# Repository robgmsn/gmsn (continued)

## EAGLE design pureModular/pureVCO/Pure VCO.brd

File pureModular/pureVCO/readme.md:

DESIGN STATUS: Awaiting testing - Ready for beta testing.

VCO Updated to V3.1 14/04/21.

Mixer section changed from Average to Sum. Mix Out is now inversion of individual outs. Might be useful?
Resistor values around mixer section reduced to 10k, inline with low noise techniques.

To do:
Final test build

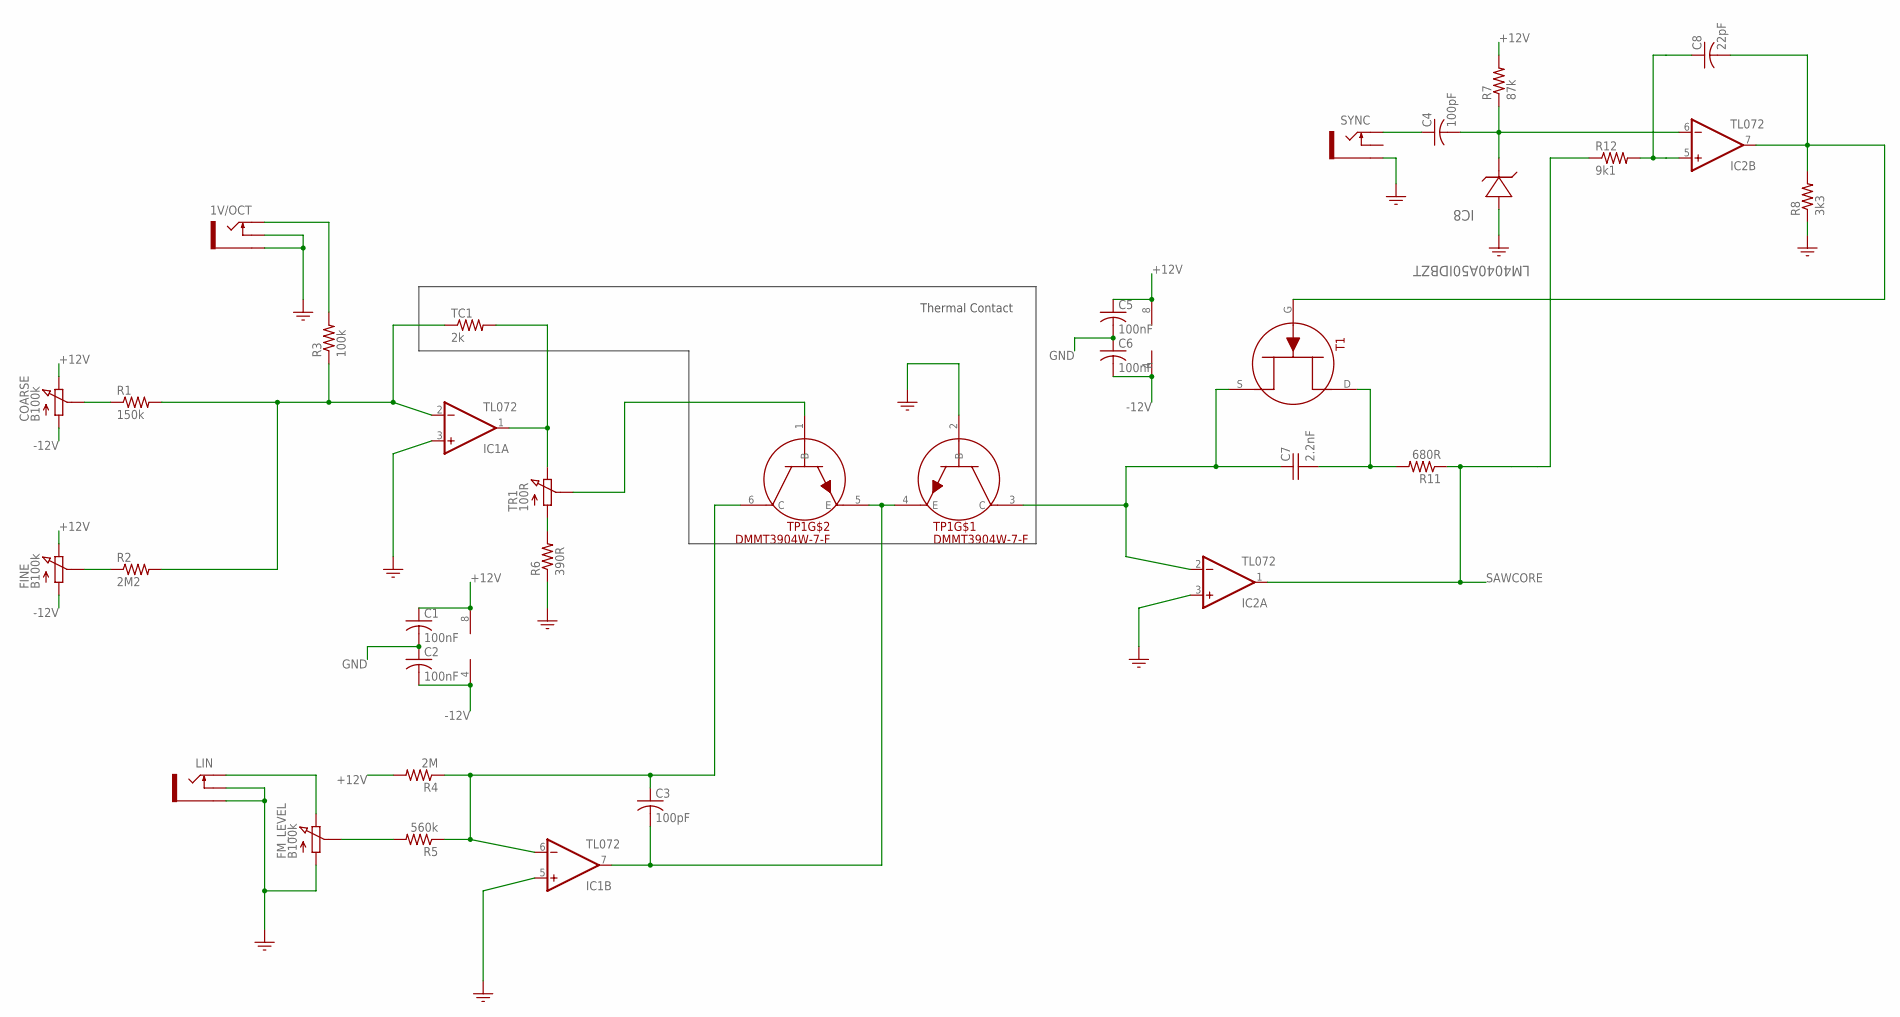
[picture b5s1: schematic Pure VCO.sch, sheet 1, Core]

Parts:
1V/OCT: PJ301M-12
C1, C2, C5, C6: 100nF; C0805
C3, C4: 100pF; C0805
C7: 2.2nF; POLY_CAP
C8: 22pF; C0805
COARSE: B100k; POT_9MM_RED_KNOB
FINE: B100k; POT_9MM_RED_MXR_KNOB
FM_LEVEL: B100k; POT_9MM_GREEN_KNOB
IC1, IC2: TL072; SO08
IC8: LM4040A50IDBZT; SOT95P237X112-3N
LIN: PJ301M-12
R1: 150k; R0805
R2: 2M2; R0805
R3: 100k; R0805
R4: 2M; R0805
R5: 560k; R0805
R6: 390R; R0805
R7: 87k; R0805
R8: 3k3; R0805
R11: 680R; R0805
R12: 9k1; R0805
SYNC: PJ301M-12
T1: MMBFJ309; N_CHN
TC1: 2k; 0207/8.5
TP1: DMMT3904W-7-F; TRANS_PAIR
TR1: 100R; TRIMMER_TH

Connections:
+12V: C1.1, C5.1, COARSE.P$3 (3), FINE.P$3 (3), IC1.8 (V+), IC2.8 (V+), R4.2, R7.2; also elsewhere on the board
-12V: C2.2, C6.2, COARSE.P$1 (1), FINE.P$1 (1), IC1.4 (V-), IC2.4 (V-); also elsewhere on the board
GND: 1V/OCT.GND (SLEEVE), 1V/OCT.NORM (SWITCH), C1.2, C2.1, C5.2, C6.1, FM_LEVEL.P$1 (1), IC1.3 (+IN), IC1.5 (+IN), IC2.3 (+IN), IC8.2 (ANODE), LIN.GND (SLEEVE), LIN.NORM (SWITCH), R6.1, R8.1, SYNC.GND (SLEEVE), TP1.2 (B); also elsewhere on the board
unnamed: COARSE.P$2 (2), R1.1
unnamed: IC1.2 (-IN), R1.2, R2.2, R3.1, TC1.1
unnamed: FINE.P$2 (2), R2.1
unnamed: IC1.1 (OUT), TC1.2, TR1.3
unnamed: R6.2, TR1.1
unnamed: 1V/OCT.TIP, R3.2
unnamed: TP1.1 (B), TR1.2
unnamed: C7.2 (-), R11.2, T1.D
unnamed: C3.1, IC1.6 (-IN), R4.1, R5.1, TP1.6 (C)
unnamed: C7.1 (+), IC2.2 (-IN), T1.S, TP1.3 (C)
unnamed: FM_LEVEL.P$3 (3), LIN.TIP
unnamed: C8.1, IC2.5 (+IN), R12.2
unnamed: FM_LEVEL.P$2 (2), R5.2
unnamed: C3.2, IC1.7 (OUT), TP1.4 (E), TP1.5 (E)
unnamed: C8.2, IC2.7 (OUT), R8.2, T1.G
unnamed: C4.1, SYNC.TIP
unnamed: C4.2, IC2.6 (-IN), IC8.1 (CATHODE), R7.1
SAWCORE: IC2.1 (OUT), R11.1, R12.1; also elsewhere on the board

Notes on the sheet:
Thermal Contact

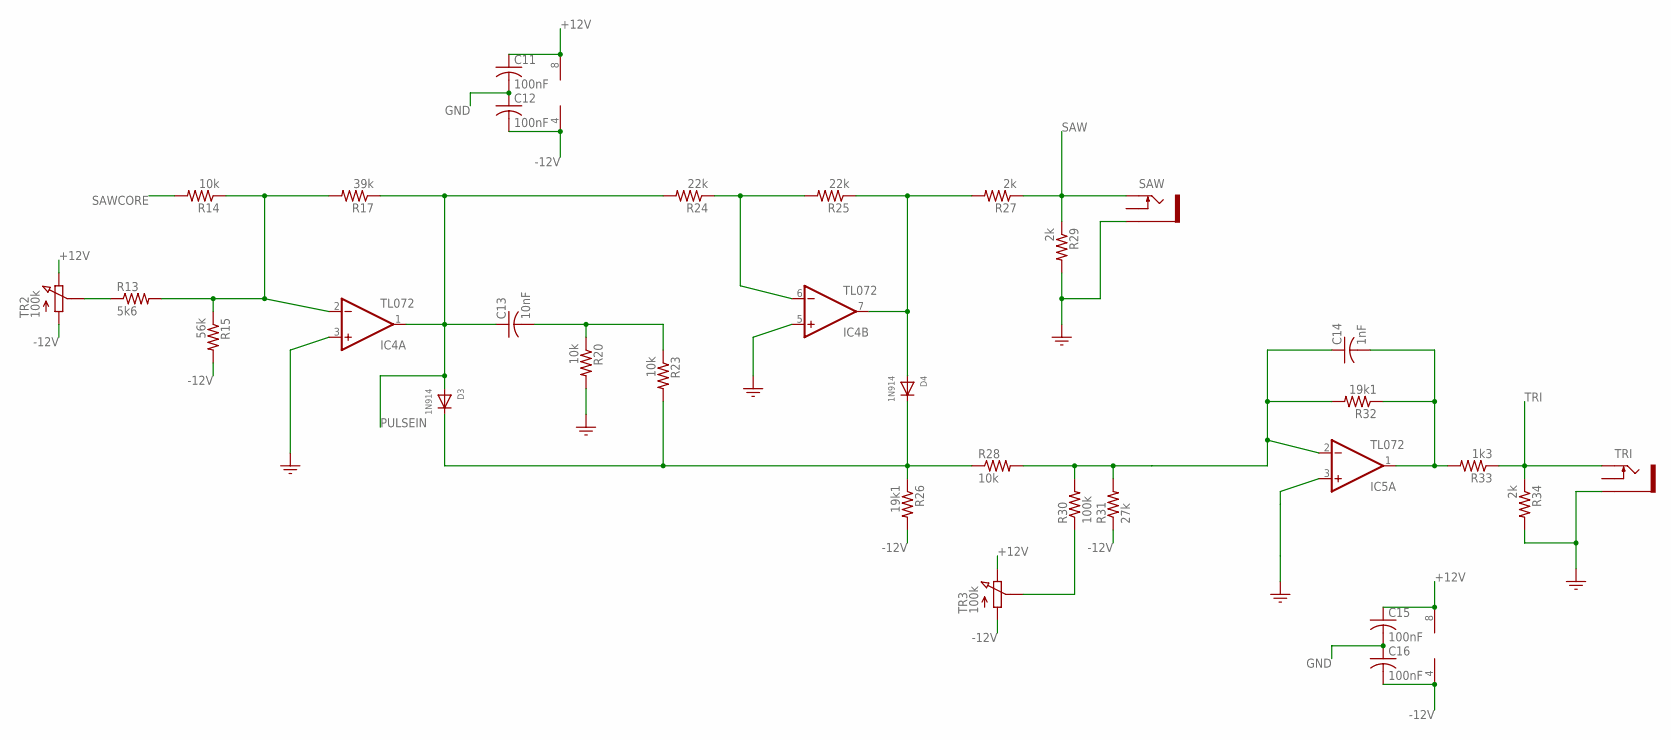
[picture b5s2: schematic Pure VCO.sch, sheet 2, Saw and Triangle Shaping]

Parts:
C11, C12, C15, C16: 100nF; C0805
C13: 10nF; C0805
C14: 1nF; C0805
D3, D4: 1N914; SOD-323F
IC4, IC5: TL072; SO08
R13: 5k6; R0805
R14, R20, R23, R28: 10k; R0805
R15: 56k; R0805
R17: 39k; R0805
R24, R25: 22k; R0805
R26, R32: 19k1; R0805
R27, R29, R34: 2k; R0805
R30: 100k; R0805
R31: 27k; R0805
R33: 1k3; R0805
SAW: PJ301M-12
TR2, TR3: 100k; TRIMMER_TH
TRI: PJ301M-12

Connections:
+12V: C11.1, C15.1, IC4.8 (V+), IC5.8 (V+), TR2.3, TR3.3; also elsewhere on the board
-12V: C12.2, C16.2, IC4.4 (V-), IC5.4 (V-), R15.2, R26.2, R31.1, TR2.1, TR3.1; also elsewhere on the board
GND: C11.2, C12.1, C15.2, C16.1, IC4.3 (+IN), IC4.5 (+IN), IC5.3 (+IN), R20.2, R29.2, R34.2, SAW.GND (SLEEVE), TRI.GND (SLEEVE); also elsewhere on the board
unnamed: R13.1, TR2.2
unnamed: IC4.2 (-IN), R13.2, R14.1, R15.1, R17.2
unnamed: C13.2, R20.1, R23.1
unnamed: R30.1, TR3.2
unnamed: IC4.6 (-IN), R24.1, R25.2
unnamed: D4.A, IC4.7 (OUT), R25.1, R27.2
unnamed: D3.C, D4.C, R23.2, R26.1, R28.1
unnamed: C14.1, IC5.2 (-IN), R28.2, R30.2, R31.2, R32.2
unnamed: C14.2, IC5.1 (OUT), R32.1, R33.2
PULSEIN: C13.1, D3.A, IC4.1 (OUT), R17.1, R24.2; also elsewhere on the board
SAW: R27.1, R29.1, SAW.TIP; also elsewhere on the board
SAWCORE: R14.2; also elsewhere on the board
TRI: R33.1, R34.1, TRI.TIP; also elsewhere on the board

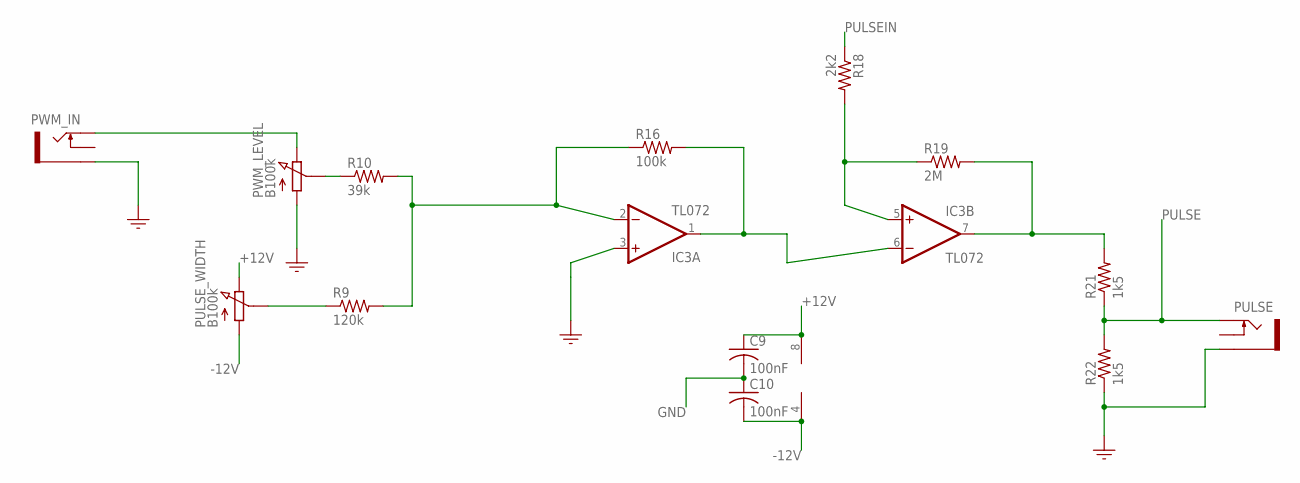
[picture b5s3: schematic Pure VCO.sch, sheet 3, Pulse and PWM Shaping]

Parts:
C9, C10: 100nF; C0805
IC3: TL072; SO08
PULSE: PJ301M-12
PULSE_WIDTH: B100k; POT_9MM_YELLOW_KNOB
PWM_IN: PJ301M-12
PWM_LEVEL: B100k; POT_9MM_GREEN_KNOB
R9: 120k; R0805
R10: 39k; R0805
R16: 100k; R0805
R18: 2k2; R0805
R19: 2M; R0805
R21, R22: 1k5; R0805

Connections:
+12V: C9.1, IC3.8 (V+), PULSE_WIDTH.P$3 (3); also elsewhere on the board
-12V: C10.2, IC3.4 (V-), PULSE_WIDTH.P$1 (1); also elsewhere on the board
GND: C9.2, C10.1, IC3.3 (+IN), PULSE.GND (SLEEVE), PWM_IN.GND (SLEEVE), PWM_LEVEL.P$1 (1), R22.1; also elsewhere on the board
unnamed: IC3.1 (OUT), IC3.6 (-IN), R16.2
unnamed: IC3.5 (+IN), R18.2, R19.1
unnamed: IC3.7 (OUT), R19.2, R21.2
unnamed: PULSE_WIDTH.P$2 (2), R9.1
unnamed: PWM_IN.TIP, PWM_LEVEL.P$3 (3)
unnamed: IC3.2 (-IN), R9.2, R10.2, R16.1
unnamed: PWM_LEVEL.P$2 (2), R10.1
PULSE: PULSE.TIP, R21.1, R22.2; also elsewhere on the board
PULSEIN: R18.1; also elsewhere on the board

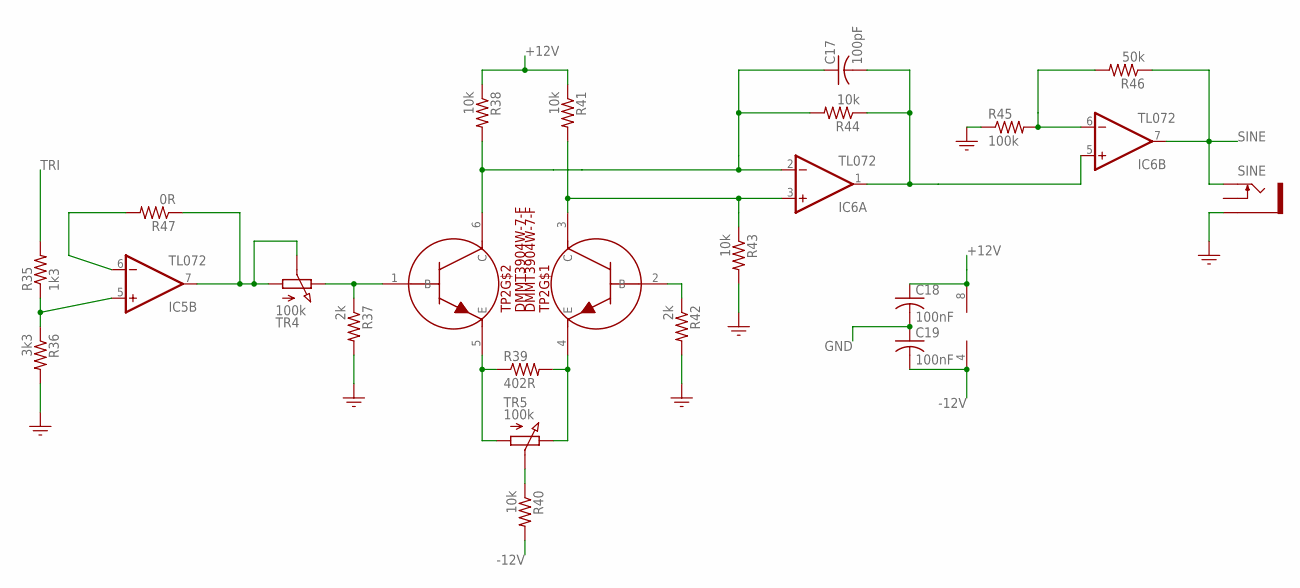
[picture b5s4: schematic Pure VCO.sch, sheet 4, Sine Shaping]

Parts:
C17: 100pF; C0805
C18, C19: 100nF; C0805
IC5, IC6: TL072; SO08
R35: 1k3; R0805
R36: 3k3; R0805
R37, R42: 2k; R0805
R38, R40, R41, R43, R44: 10k; R0805
R39: 402R; R0805
R45: 100k; R0805
R46: 50k; R0805
R47: 0R; R0805
SINE: PJ301M-12
TP2: DMMT3904W-7-F; TRANS_PAIR
TR4, TR5: 100k; TRIMMER_TH

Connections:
+12V: C18.1, IC6.8 (V+), R38.1, R41.1; also elsewhere on the board
-12V: C19.2, IC6.4 (V-), R40.2; also elsewhere on the board
GND: C18.2, C19.1, R36.2, R37.2, R42.2, R43.2, R45.1, SINE.GND (SLEEVE); also elsewhere on the board
unnamed: C17.1, IC6.2 (-IN), R38.2, R44.2, TP2.6 (C)
unnamed: IC5.6 (-IN), R47.2
unnamed: IC5.7 (OUT), R47.1, TR4.1, TR4.2
unnamed: R37.1, TP2.1 (B), TR4.3
unnamed: R39.1, TP2.5 (E), TR5.1
unnamed: R39.2, TP2.4 (E), TR5.3
unnamed: R40.1, TR5.2
unnamed: R42.1, TP2.2 (B)
unnamed: IC6.3 (+IN), R41.2, R43.1, TP2.3 (C)
unnamed: IC5.5 (+IN), R35.1, R36.1
unnamed: IC6.6 (-IN), R45.2, R46.2
SINE: IC6.7 (OUT), R46.1, SINE.TIP; also elsewhere on the board
SINE_PRE1: C17.2, IC6.1 (OUT), IC6.5 (+IN), R44.1
TRI: R35.2; also elsewhere on the board

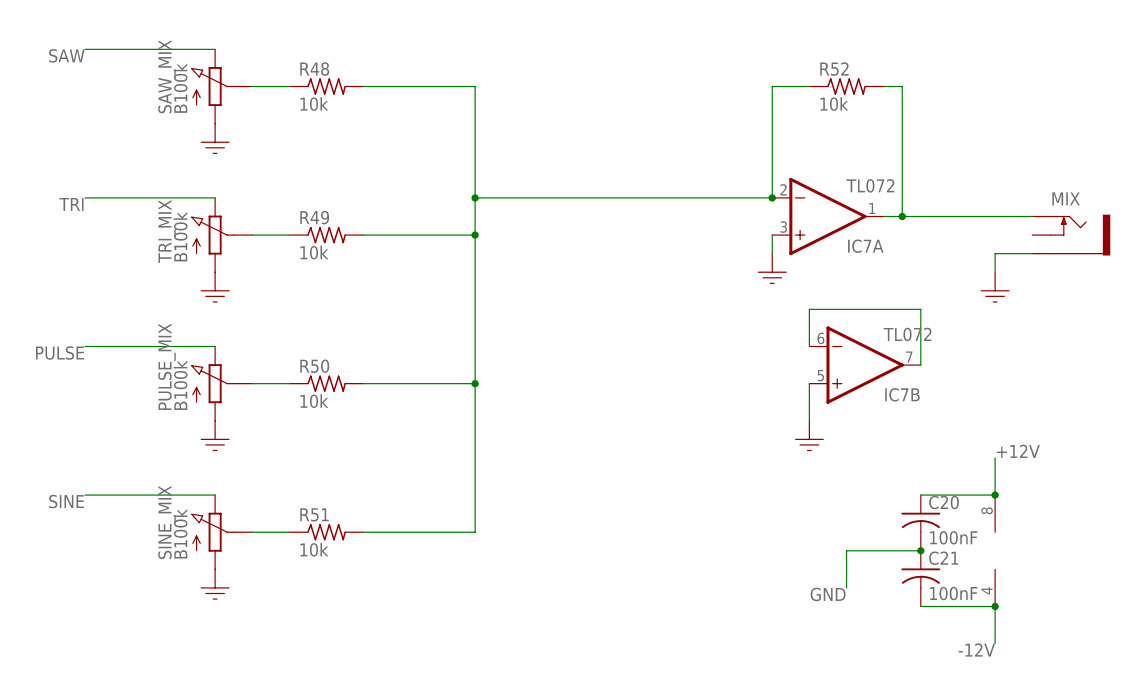
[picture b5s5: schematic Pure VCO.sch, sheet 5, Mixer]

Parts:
C20, C21: 100nF; C0805
IC7: TL072; SO08
MIX: PJ301M-12
PULSE_MIX: B100k; POT_9MM_BLUE_KNOB
R48, R49, R50, R51, R52: 10k; R0805
SAW_MIX: B100k; POT_9MM_BLUE_KNOB
SINE_MIX: B100k; POT_9MM_BLUE_KNOB
TRI_MIX: B100k; POT_9MM_BLUE_KNOB

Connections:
+12V: C20.1, IC7.8 (V+); also elsewhere on the board
-12V: C21.2, IC7.4 (V-); also elsewhere on the board
GND: C20.2, C21.1, IC7.3 (+IN), IC7.5 (+IN), MIX.GND (SLEEVE), PULSE_MIX.P$1 (1), SAW_MIX.P$1 (1), SINE_MIX.P$1 (1), TRI_MIX.P$1 (1); also elsewhere on the board
unnamed: IC7.6 (-IN), IC7.7 (OUT)
unnamed: R48.1, SAW_MIX.P$2 (2)
unnamed: R49.1, TRI_MIX.P$2 (2)
unnamed: PULSE_MIX.P$2 (2), R50.1
unnamed: R51.1, SINE_MIX.P$2 (2)
unnamed: IC7.2 (-IN), R48.2, R49.2, R50.2, R51.2, R52.1
unnamed: IC7.1 (OUT), MIX.TIP, R52.2
PULSE: PULSE_MIX.P$3 (3); also elsewhere on the board
SAW: SAW_MIX.P$3 (3); also elsewhere on the board
SINE: SINE_MIX.P$3 (3); also elsewhere on the board
TRI: TRI_MIX.P$3 (3); also elsewhere on the board

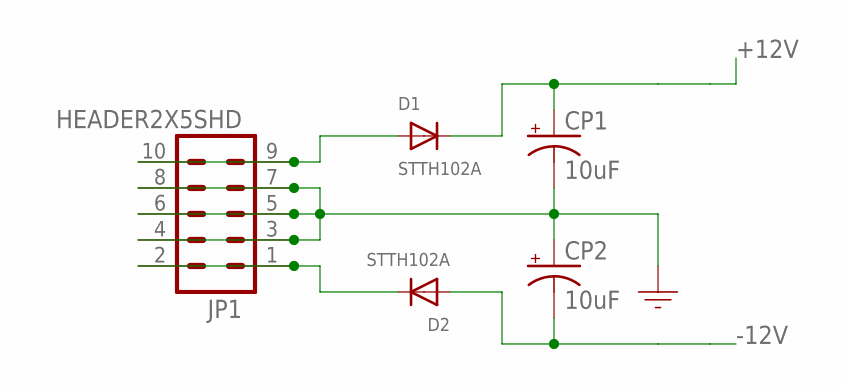
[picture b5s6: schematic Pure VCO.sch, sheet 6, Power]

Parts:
CP1, CP2: 10uF; 153CLV-0505
D1, D2: STTH102A; SMADIODE
JP1: HEADER2X5SHD; 2X5-SHROUDED

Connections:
+12V: CP1.+, D1.C; also elsewhere on the board
-12V: CP2.-, D2.A; also elsewhere on the board
GND: CP1.-, CP2.+, JP1.3, JP1.4, JP1.5, JP1.6, JP1.7, JP1.8; also elsewhere on the board
unnamed: D1.A, JP1.9, JP1.10
unnamed: D2.C, JP1.1, JP1.2

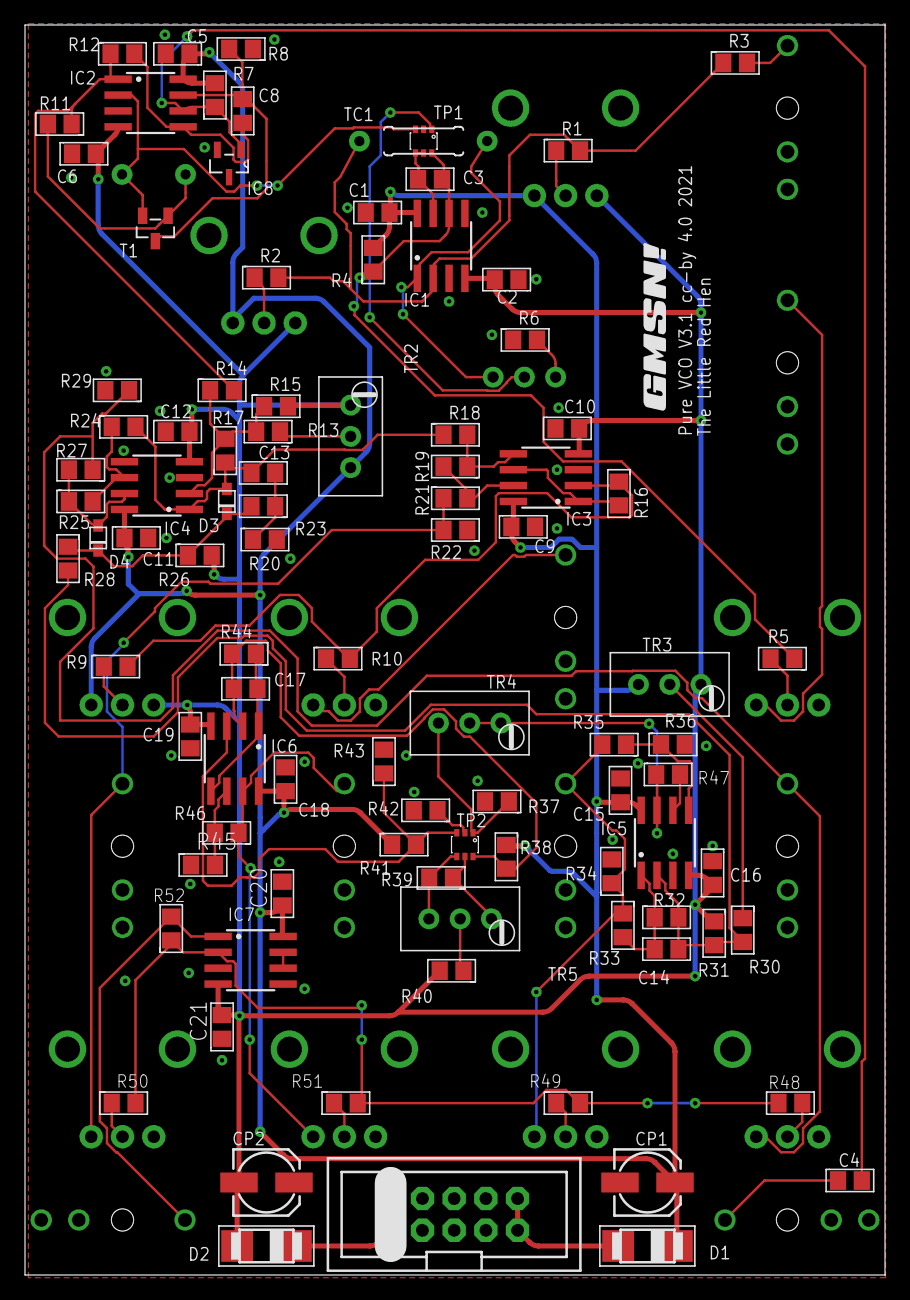
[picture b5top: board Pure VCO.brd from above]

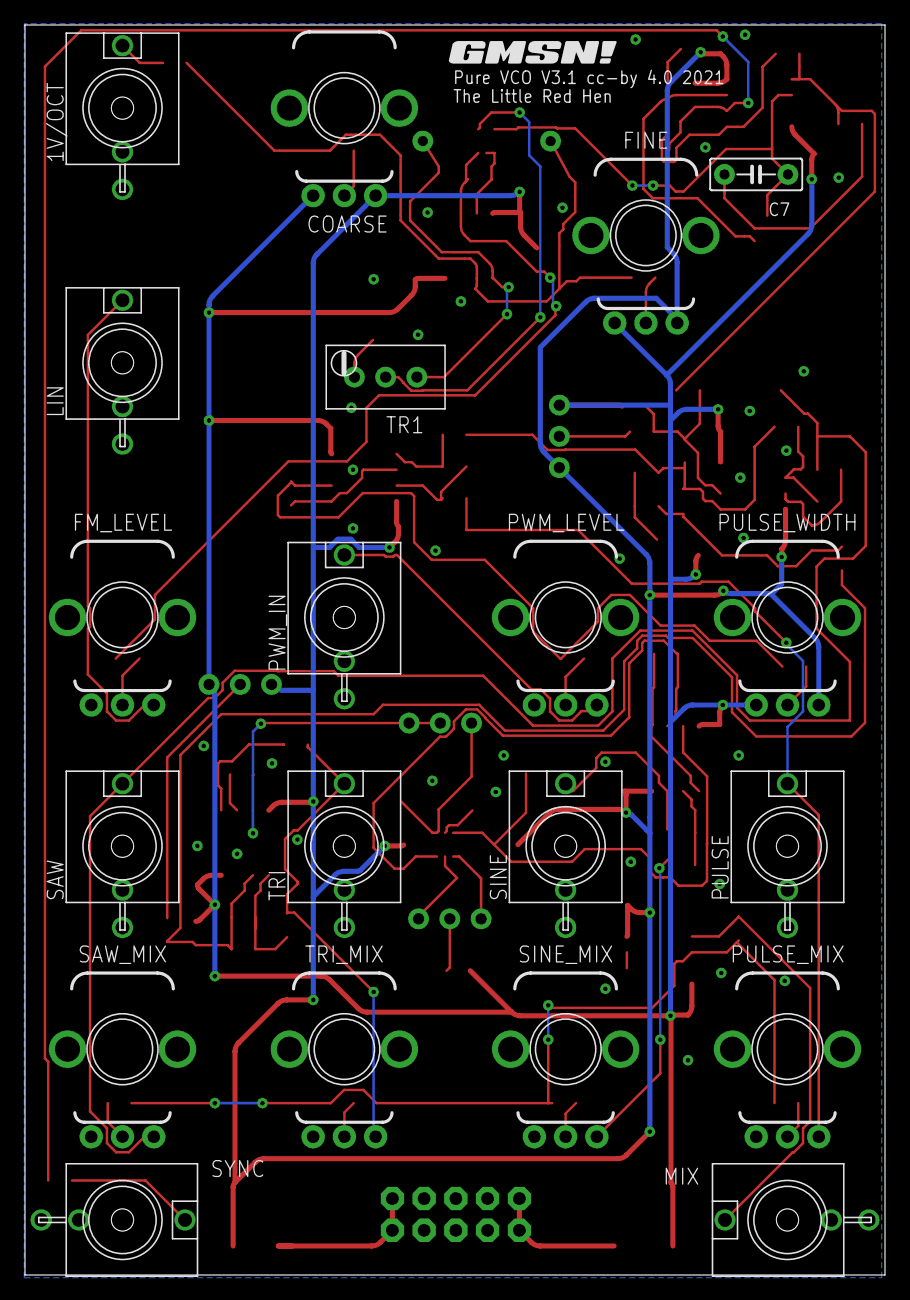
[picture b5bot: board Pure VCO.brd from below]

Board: 2 copper layers, 68.8 x 100.0 mm, 117 parts (21 on the bottom side), 63 nets.

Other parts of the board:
U$1, U$2: GMSN!_LOGO

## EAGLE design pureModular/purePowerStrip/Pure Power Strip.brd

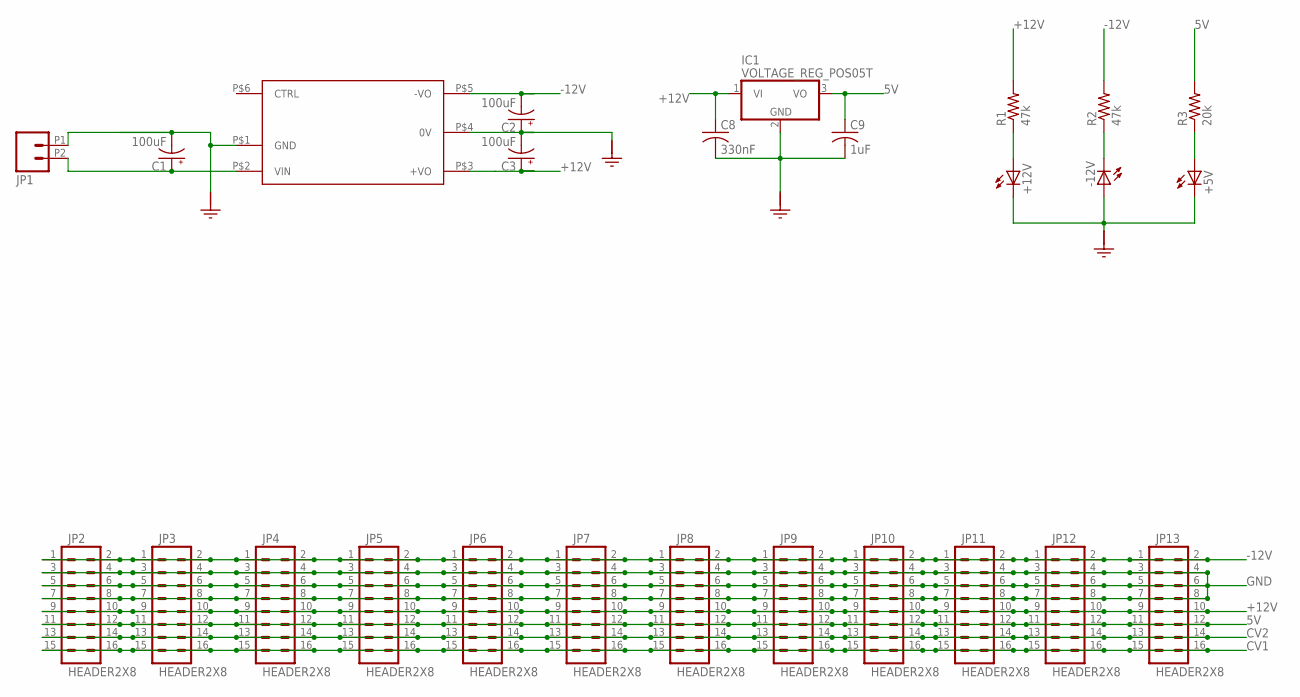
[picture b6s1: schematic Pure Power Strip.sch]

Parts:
+5V, +12V: LED5MM
-12V: LED5MM
C1, C2, C3: 100uF; 0511/2.24
C8: 330nF; C025-024X044
C9: 1uF; C025-024X044
IC1: VOLTAGE_REG_POS05T; TO220H
JP1: HEADER1X25MM_SCREWTERM; 1X02_5MM_SCREWTERM
JP2, JP3, JP4, JP5, JP6, JP7, JP8, JP9, JP10, JP11, JP12, JP13: HEADER2X8; POWER_SHROUDED
R1, R2: 47k; 0207/8.5
R3: 20k; 0207/8.5
U$1: DCDC_CONVERTER_URA241XLD-20WR3; URA241XLD-20WR3

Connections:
5V: C9.1, IC1.3 (VO), JP2.11, JP2.12, JP3.11, JP3.12, JP4.11, JP4.12, JP5.11, JP5.12, JP6.11, JP6.12, JP7.11, JP7.12, JP8.11, JP8.12, JP9.11, JP9.12, JP10.11, JP10.12, JP11.11, JP11.12, JP12.11, JP12.12, JP13.11, JP13.12, R3.2
+12V: C3.P$2 (+), C8.1, IC1.1 (VI), JP2.9, JP2.10, JP3.9, JP3.10, JP4.9, JP4.10, JP5.9, JP5.10, JP6.9, JP6.10, JP7.9, JP7.10, JP8.9, JP8.10, JP9.9, JP9.10, JP10.9, JP10.10, JP11.9, JP11.10, JP12.9, JP12.10, JP13.9, JP13.10, R1.2, U$1.P$3 (+VO)
-12V: C2.P$1 (-), JP2.1, JP2.2, JP3.1, JP3.2, JP4.1, JP4.2, JP5.1, JP5.2, JP6.1, JP6.2, JP7.1, JP7.2, JP8.1, JP8.2, JP9.1, JP9.2, JP10.1, JP10.2, JP11.1, JP11.2, JP12.1, JP12.2, JP13.1, JP13.2, R2.2, U$1.P$5 (-VO)
CV1: JP2.15, JP2.16, JP3.15, JP3.16, JP4.15, JP4.16, JP5.15, JP5.16, JP6.15, JP6.16, JP7.15, JP7.16, JP8.15, JP8.16, JP9.15, JP9.16, JP10.15, JP10.16, JP11.15, JP11.16, JP12.15, JP12.16, JP13.15, JP13.16
CV2: JP2.13, JP2.14, JP3.13, JP3.14, JP4.13, JP4.14, JP5.13, JP5.14, JP6.13, JP6.14, JP7.13, JP7.14, JP8.13, JP8.14, JP9.13, JP9.14, JP10.13, JP10.14, JP11.13, JP11.14, JP12.13, JP12.14, JP13.13, JP13.14
GND: +5V.K (C), +12V.K (C), -12V.A, C1.P$1 (-), C2.P$2 (+), C3.P$1 (-), C8.2, C9.2, IC1.2 (GND), JP1.P1 (1), JP2.3, JP2.4, JP2.5, JP2.6, JP2.7, JP2.8, JP3.3, JP3.4, JP3.5, JP3.6, JP3.7, JP3.8, JP4.3, JP4.4, JP4.5, JP4.6, JP4.7, JP4.8, JP5.3, JP5.4, JP5.5, JP5.6, JP5.7, JP5.8, JP6.3, JP6.4, JP6.5, JP6.6, JP6.7, JP6.8, JP7.3, JP7.4, JP7.5, JP7.6, JP7.7, JP7.8, JP8.3, JP8.4, JP8.5, JP8.6, JP8.7, JP8.8, JP9.3, JP9.4, JP9.5, JP9.6, JP9.7, JP9.8, JP10.3, JP10.4, JP10.5, JP10.6, JP10.7, JP10.8, JP11.3, JP11.4, JP11.5, JP11.6, JP11.7, JP11.8, JP12.3, JP12.4, JP12.5, JP12.6, JP12.7, JP12.8, JP13.3, JP13.4, JP13.5, JP13.6, JP13.7, JP13.8, U$1.P$1 (GND), U$1.P$4 (0V)
unnamed: C1.P$2 (+), JP1.P2 (2), U$1.P$2 (VIN)
unnamed: +12V.A, R1.1
unnamed: -12V.K (C), R2.1
unnamed: +5V.A, R3.1

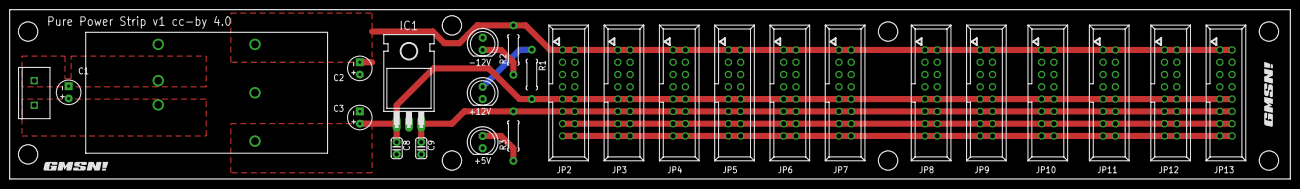
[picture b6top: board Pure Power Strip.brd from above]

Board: 2 copper layers, 264.8 x 35.0 mm, 28 parts (0 on the bottom side), 10 nets.

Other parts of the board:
U$14, U$15: GMSN!_LOGO

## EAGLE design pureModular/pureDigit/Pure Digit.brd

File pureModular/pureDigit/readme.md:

Awaiting Testing - Not for public consumption.

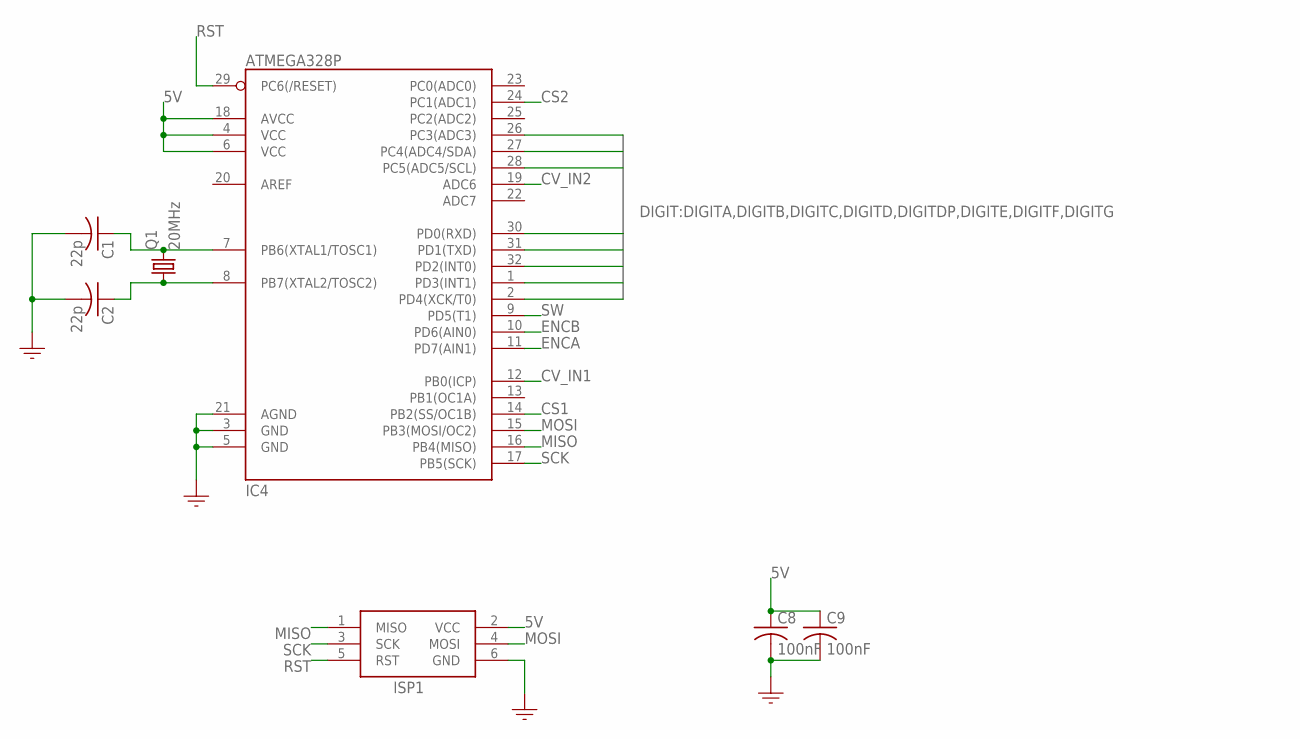
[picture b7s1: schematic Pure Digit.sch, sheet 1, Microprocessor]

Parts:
C1, C2: 22p; C0805
C8, C9: 100nF; C0805
IC4: ATMEGA328P; TQFP32-08
ISP1: HEADER2X3-6; AVRISP
Q1: 20MHz; SM49

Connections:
5V: C8.1, C9.1, IC4.4 (VCC), IC4.6 (VCC), IC4.18 (AVCC), ISP1.2 (VCC); also elsewhere on the board
CS1: IC4.14 (PB2(SS/OC1B)); also elsewhere on the board
CS2: IC4.24 (PC1(ADC1)); also elsewhere on the board
CV_IN1: IC4.12 (PB0(ICP)); also elsewhere on the board
CV_IN2: IC4.19 (ADC6); also elsewhere on the board
DIGITA: IC4.30 (PD0(RXD)); also elsewhere on the board
DIGITB: IC4.28 (PC5(ADC5/SCL)); also elsewhere on the board
DIGITC: IC4.27 (PC4(ADC4/SDA)); also elsewhere on the board
DIGITD: IC4.26 (PC3(ADC3)); also elsewhere on the board
DIGITDP: IC4.1 (PD3(INT1)); also elsewhere on the board
DIGITE: IC4.2 (PD4(XCK/T0)); also elsewhere on the board
DIGITF: IC4.32 (PD2(INT0)); also elsewhere on the board
DIGITG: IC4.31 (PD1(TXD)); also elsewhere on the board
ENCA: IC4.11 (PD7(AIN1)); also elsewhere on the board
ENCB: IC4.10 (PD6(AIN0)); also elsewhere on the board
GND: C1.2, C2.2, C8.2, C9.2, IC4.3 (GND), IC4.5 (GND), IC4.21 (AGND), ISP1.6 (GND); also elsewhere on the board
MISO: IC4.16 (PB4(MISO)), ISP1.1 (MISO); also elsewhere on the board
MOSI: IC4.15 (PB3(MOSI/OC2)), ISP1.4 (MOSI); also elsewhere on the board
unnamed: C1.1, IC4.7 (PB6(XTAL1/TOSC1)), Q1.2
unnamed: C2.1, IC4.8 (PB7(XTAL2/TOSC2)), Q1.1
RST: IC4.29 (PC6(/RESET)), ISP1.5 (RST)
SCK: IC4.17 (PB5(SCK)), ISP1.3 (SCK); also elsewhere on the board
SW: IC4.9 (PD5(T1)); also elsewhere on the board

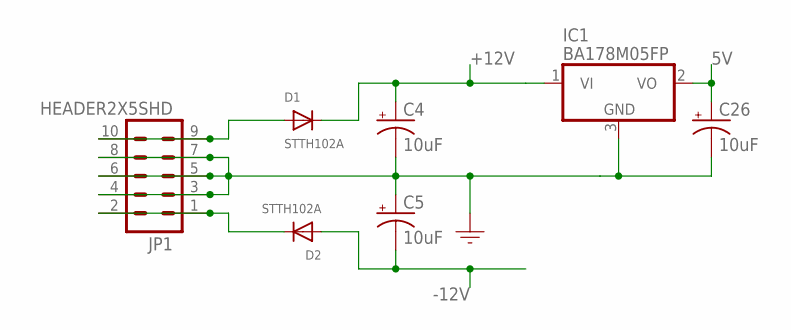
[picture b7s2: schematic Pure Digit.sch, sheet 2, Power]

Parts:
C4, C5, C26: 10uF; 153CLV-0505
D1, D2: STTH102A; SMADIODE
IC1: BA178M05FP; TO252
JP1: HEADER2X5SHD; 2X5-SHROUDED

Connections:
5V: C26.+, IC1.2 (VO); also elsewhere on the board
+12V: C4.+, D1.C, IC1.1 (VI); also elsewhere on the board
-12V: C5.-, D2.A; also elsewhere on the board
GND: C4.-, C5.+, C26.-, IC1.3 (GND), JP1.3, JP1.4, JP1.5, JP1.6, JP1.7, JP1.8; also elsewhere on the board
unnamed: D1.A, JP1.9, JP1.10
unnamed: D2.C, JP1.1, JP1.2

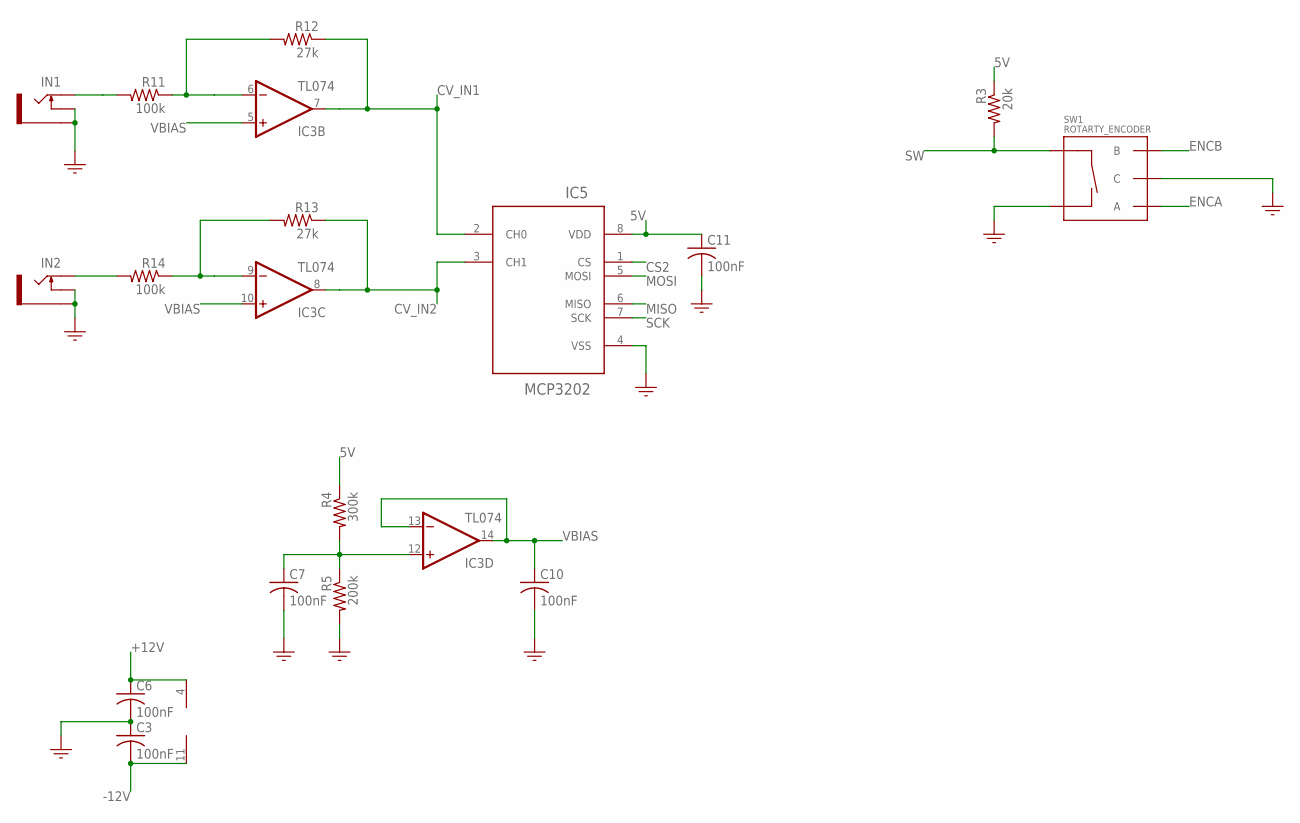
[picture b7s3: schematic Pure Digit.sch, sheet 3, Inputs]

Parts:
C3, C6, C7, C10, C11: 100nF; C0805
IC3: TL074; SO14
IC5: MCP3202; SOIC--8
IN1, IN2: PJ301M-12
R3: 20k; R0805
R4: 300k; R0805
R5: 200k; R0805
R11, R14: 100k; R0805
R12, R13: 27k; R0805
SW1: ROTARTY_ENCODER; ROTARY_ENC_PLAIN

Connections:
5V: C11.1, IC5.8 (VDD), R3.1, R4.1; also elsewhere on the board
+12V: C6.1, IC3.4 (V+); also elsewhere on the board
-12V: C3.2, IC3.11 (V-); also elsewhere on the board
CS2: IC5.1 (CS); also elsewhere on the board
CV_IN1: IC3.7 (OUT), IC5.2 (CH0), R12.1; also elsewhere on the board
CV_IN2: IC3.8 (OUT), IC5.3 (CH1), R13.1; also elsewhere on the board
ENCA: SW1.A; also elsewhere on the board
ENCB: SW1.B; also elsewhere on the board
GND: C3.1, C6.2, C7.2, C10.2, C11.2, IC5.4 (VSS), IN1.GND (SLEEVE), IN1.NORM (SWITCH), IN2.GND (SLEEVE), IN2.NORM (SWITCH), R5.2, SW1.C, SW1.SW-; also elsewhere on the board
MISO: IC5.6 (MISO); also elsewhere on the board
MOSI: IC5.5 (MOSI); also elsewhere on the board
unnamed: IN1.TIP, R11.2
unnamed: IN2.TIP, R14.2
unnamed: C7.1, IC3.12 (+IN), R4.2, R5.1
unnamed: IC3.6 (-IN), R11.1, R12.2
unnamed: IC3.9 (-IN), R13.2, R14.1
SCK: IC5.7 (SCK); also elsewhere on the board
SW: R3.2, SW1.SW+; also elsewhere on the board
VBIAS: C10.1, IC3.5 (+IN), IC3.10 (+IN), IC3.13 (-IN), IC3.14 (OUT)

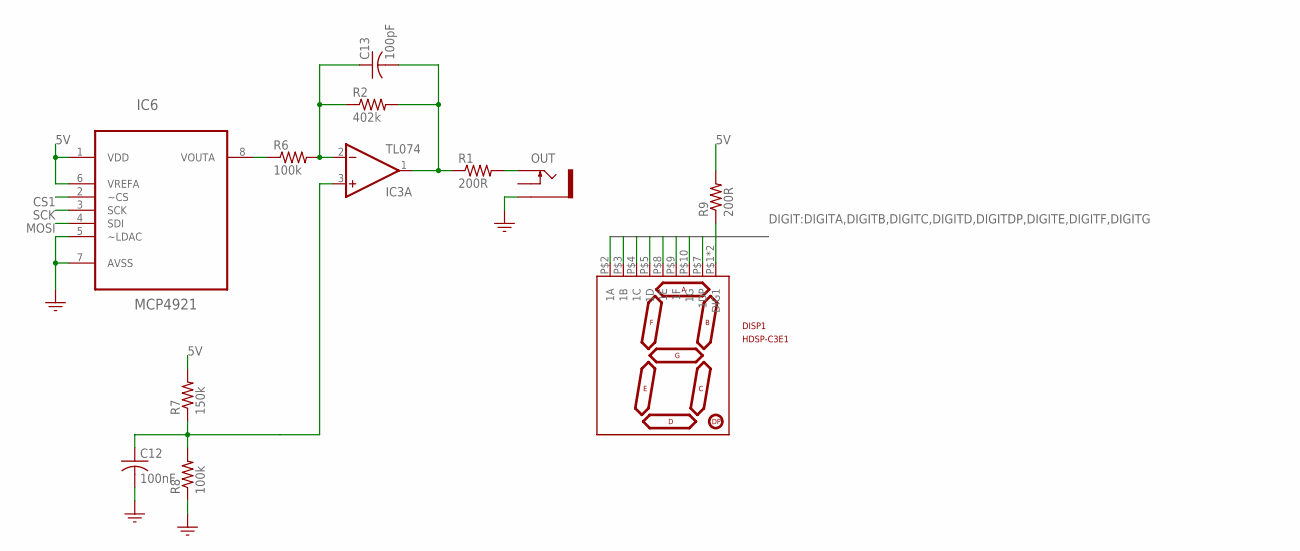
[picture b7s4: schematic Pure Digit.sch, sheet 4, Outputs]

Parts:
C12: 100nF; C0805
C13: 100pF; C0805
DISP1: HDSP-C3E1; 7-SEGMENT-1DIGIT
IC3: TL074; SO14
IC6: MCP4921; SOIC8
OUT: PJ301M-12
R1, R9: 200R; R0805
R2: 402k; R0805
R6, R8: 100k; R0805
R7: 150k; R0805

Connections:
5V: IC6.1 (VDD), IC6.6 (VREFA), R7.2, R9.2; also elsewhere on the board
CS1: IC6.2 (~CS); also elsewhere on the board
DIGITA: DISP1.P$2 (1A); also elsewhere on the board
DIGITB: DISP1.P$3 (1B); also elsewhere on the board
DIGITC: DISP1.P$4 (1C); also elsewhere on the board
DIGITD: DISP1.P$5 (1D); also elsewhere on the board
DIGITDP: DISP1.P$7 (1DP); also elsewhere on the board
DIGITE: DISP1.P$8 (1E); also elsewhere on the board
DIGITF: DISP1.P$9 (1F); also elsewhere on the board
DIGITG: DISP1.P$10 (1G); also elsewhere on the board
GND: C12.2, IC6.5 (~LDAC), IC6.7 (AVSS), OUT.GND (SLEEVE), R8.1; also elsewhere on the board
MOSI: IC6.4 (SDI); also elsewhere on the board
unnamed: C12.1, IC3.3 (+IN), R7.1, R8.2
unnamed: C13.2, IC3.1 (OUT), R1.1, R2.2
unnamed: OUT.TIP, R1.2
unnamed: IC6.8 (VOUTA), R6.1
unnamed: C13.1, IC3.2 (-IN), R2.1, R6.2
unnamed: DISP1.P$1 (DIG1), DISP1.P$6 (DIG1), R9.1
SCK: IC6.3 (SCK); also elsewhere on the board

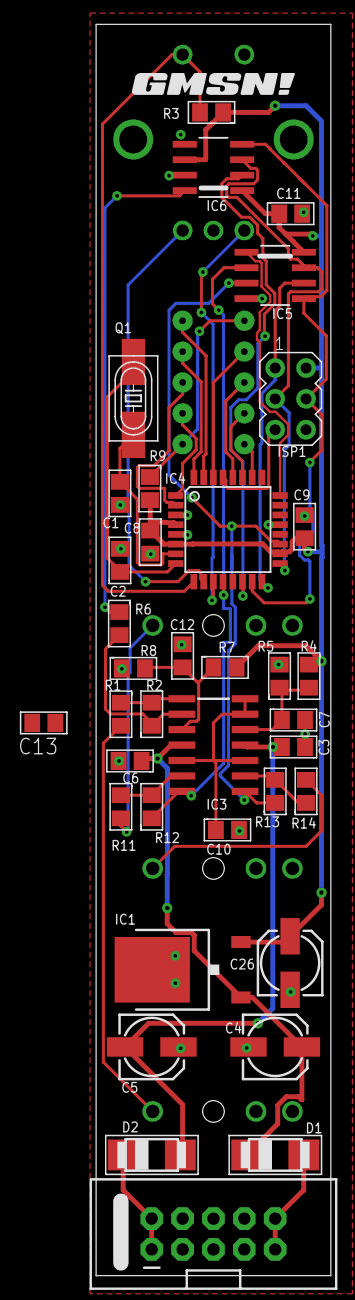
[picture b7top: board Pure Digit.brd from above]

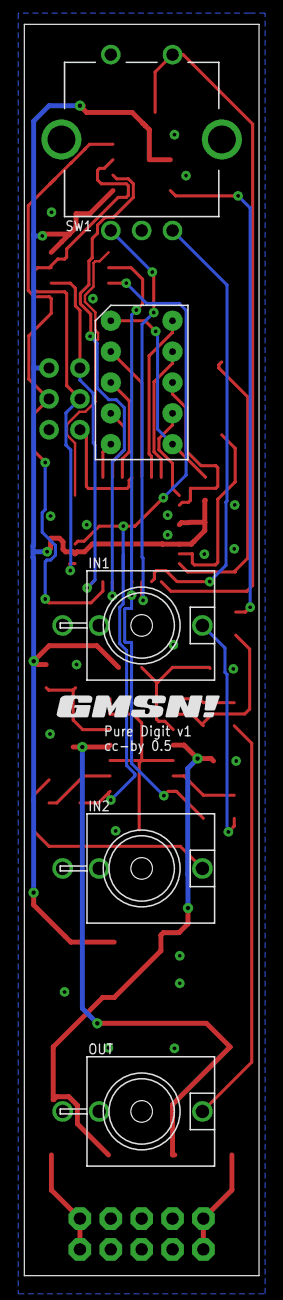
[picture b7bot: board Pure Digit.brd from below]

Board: 2 copper layers, 19.3 x 103.0 mm, 44 parts (6 on the bottom side), 39 nets.

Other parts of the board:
U$1, U$2: GMSN!_LOGO
